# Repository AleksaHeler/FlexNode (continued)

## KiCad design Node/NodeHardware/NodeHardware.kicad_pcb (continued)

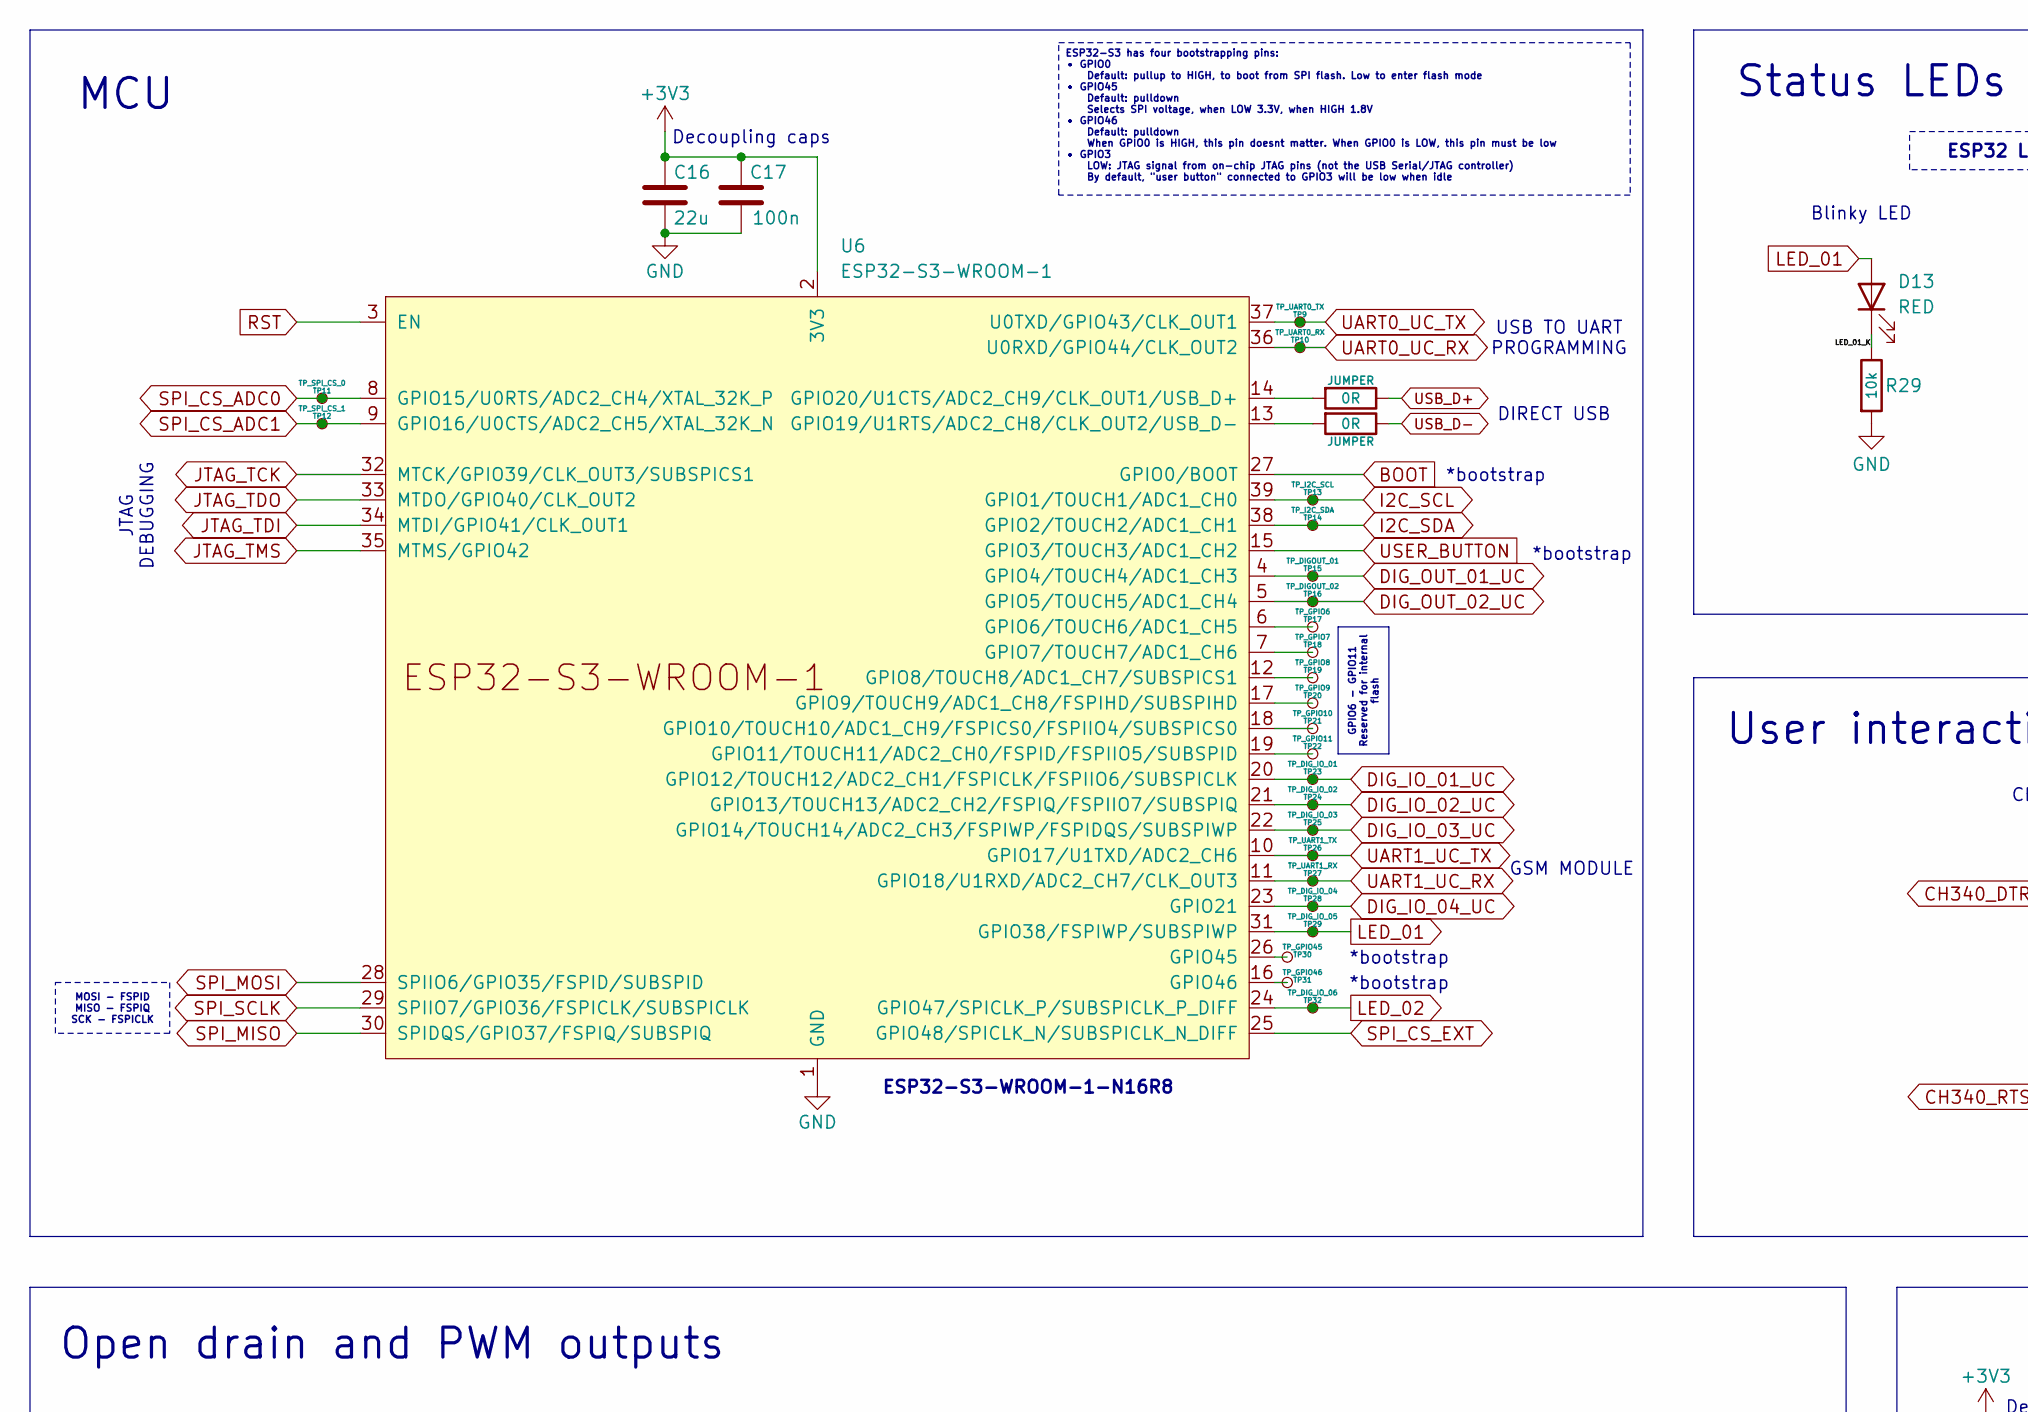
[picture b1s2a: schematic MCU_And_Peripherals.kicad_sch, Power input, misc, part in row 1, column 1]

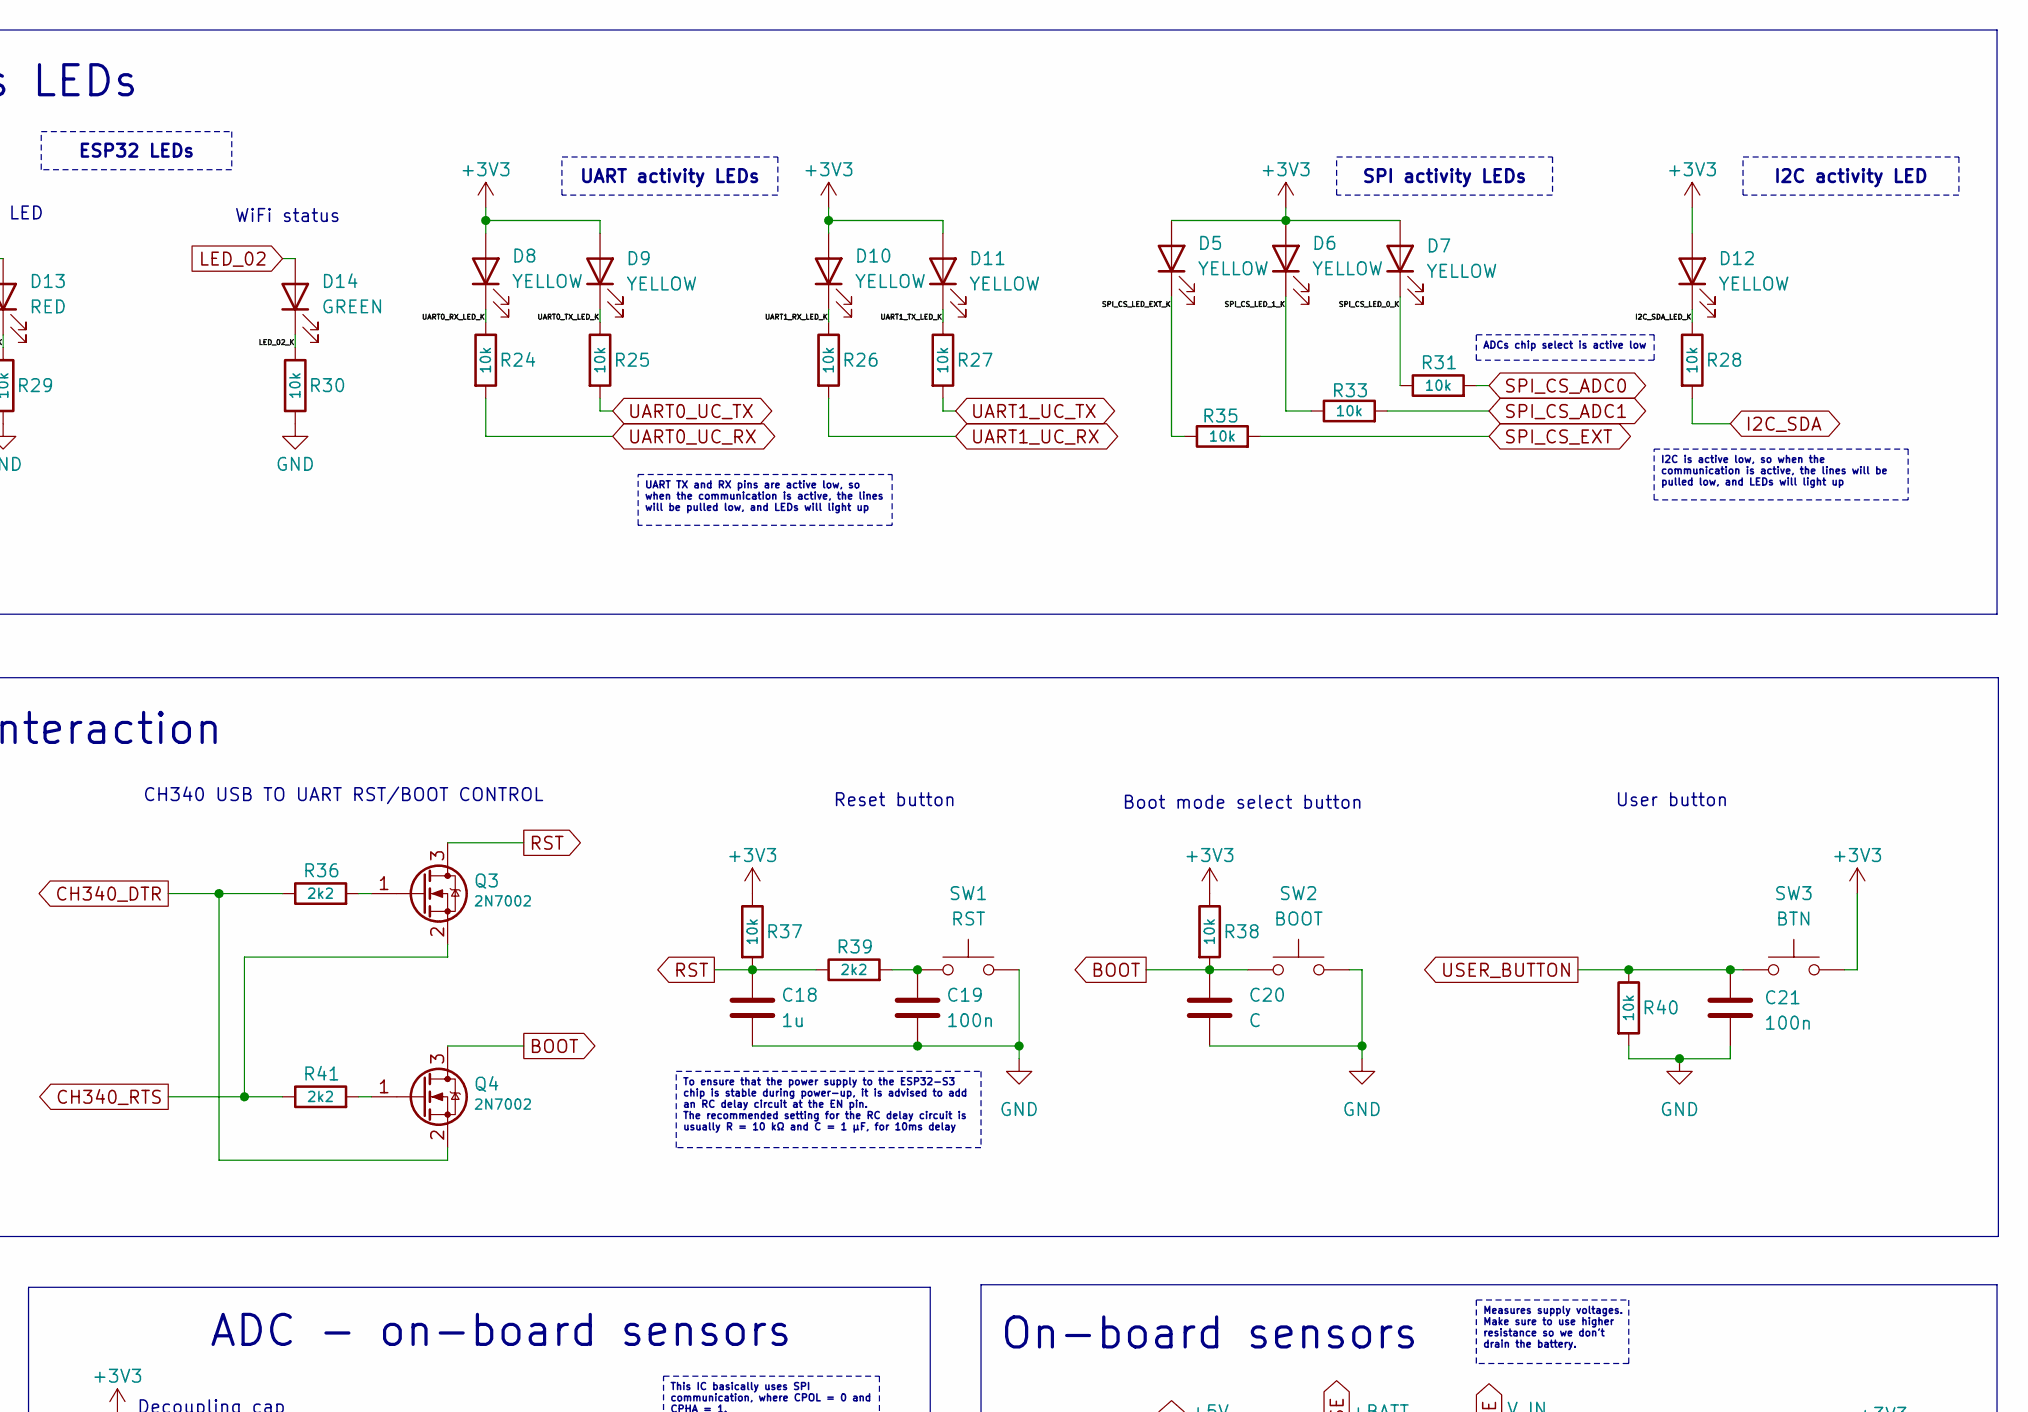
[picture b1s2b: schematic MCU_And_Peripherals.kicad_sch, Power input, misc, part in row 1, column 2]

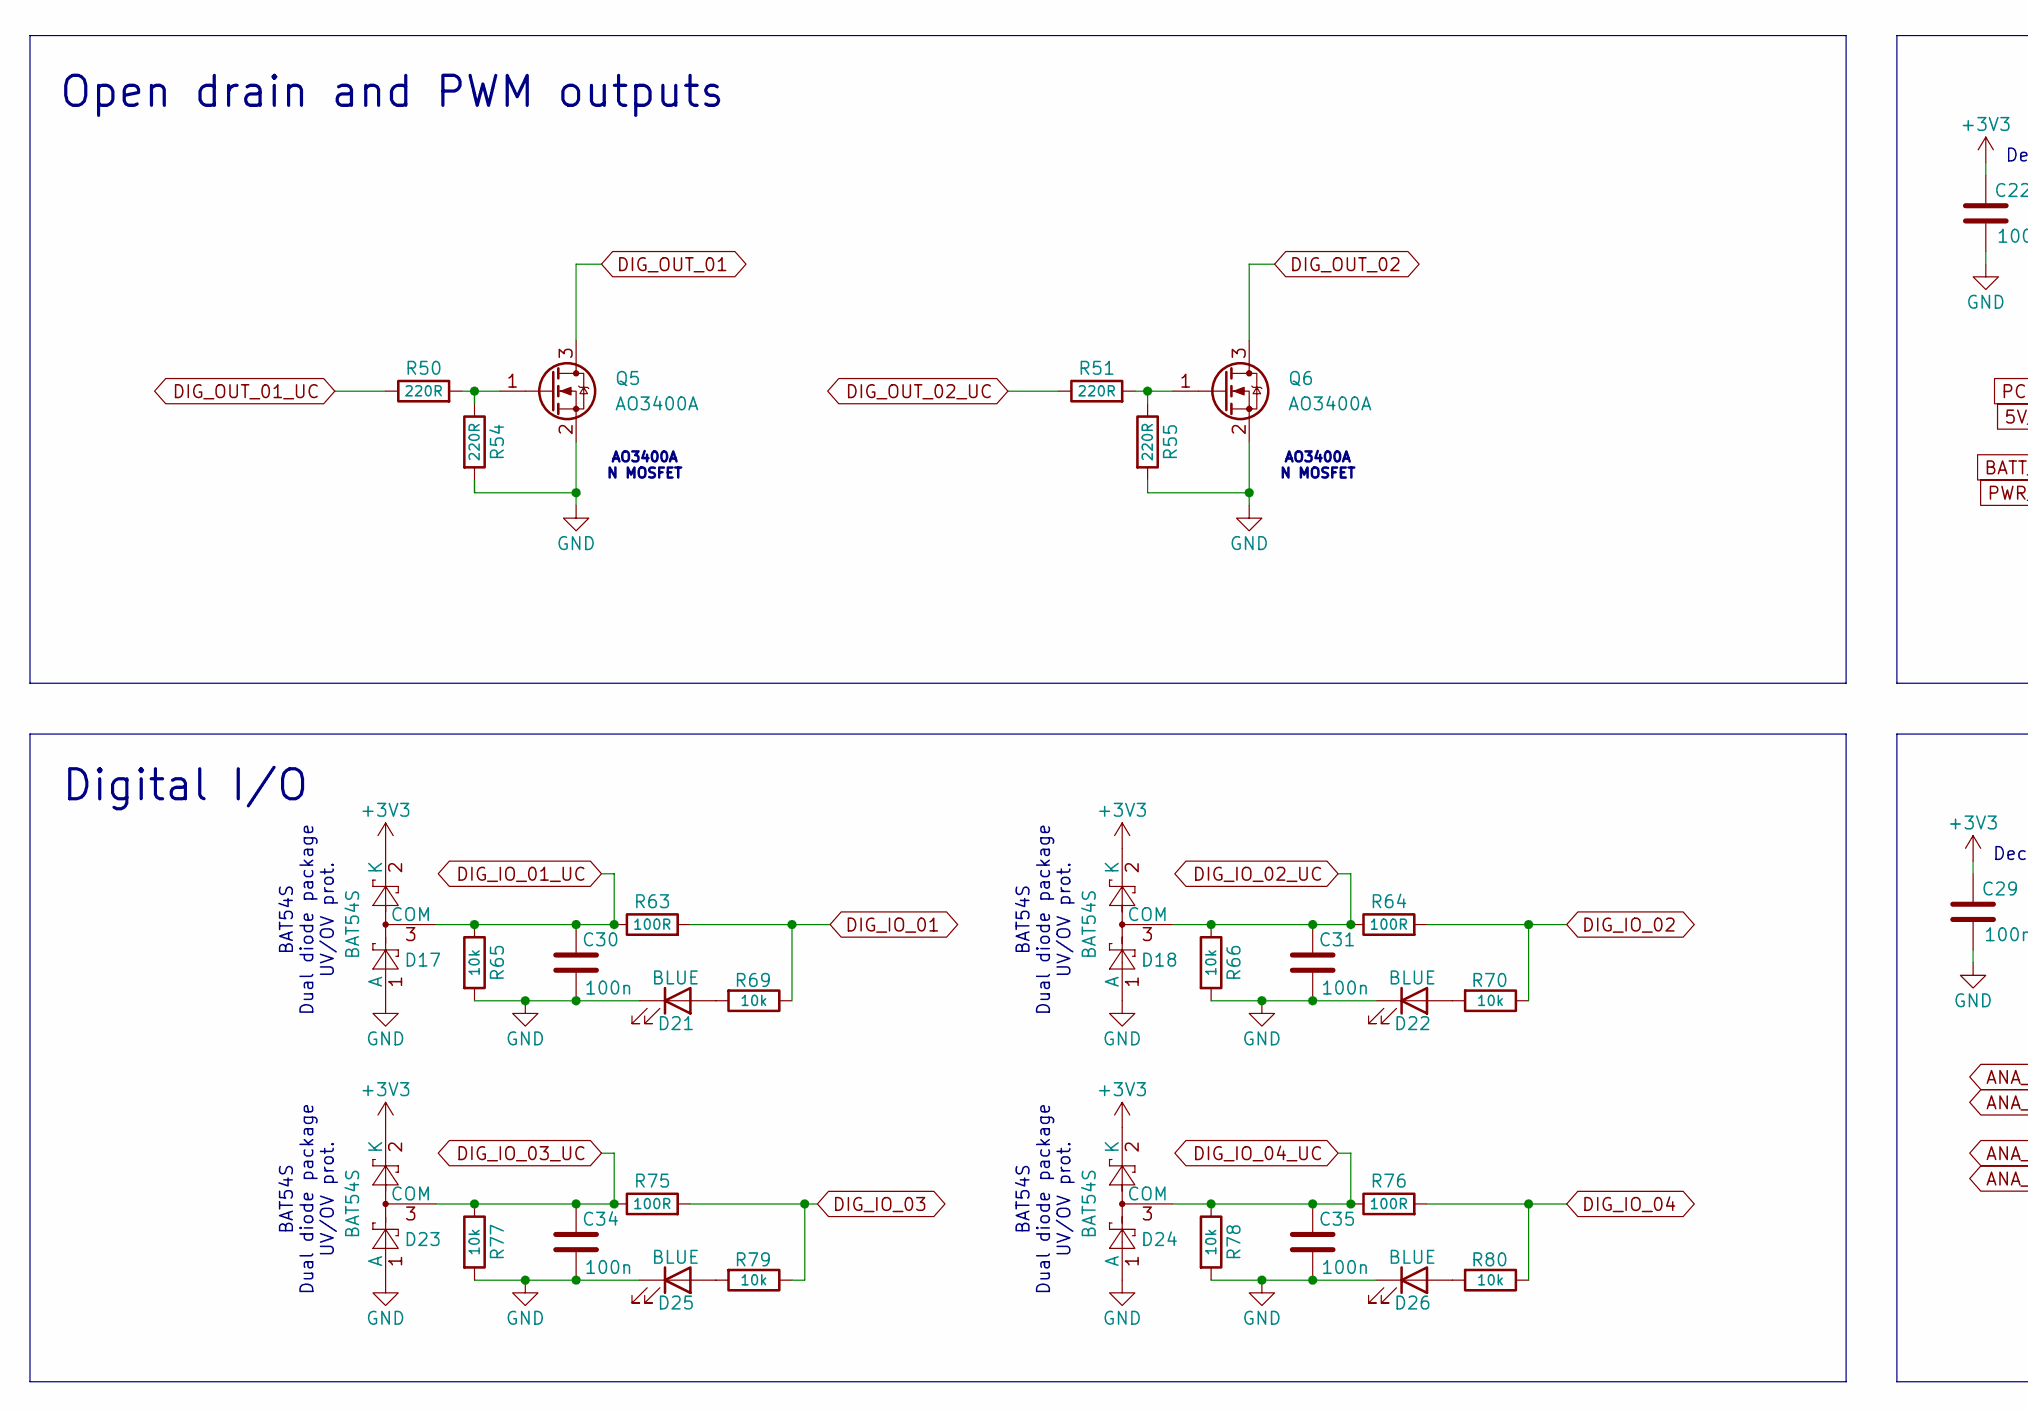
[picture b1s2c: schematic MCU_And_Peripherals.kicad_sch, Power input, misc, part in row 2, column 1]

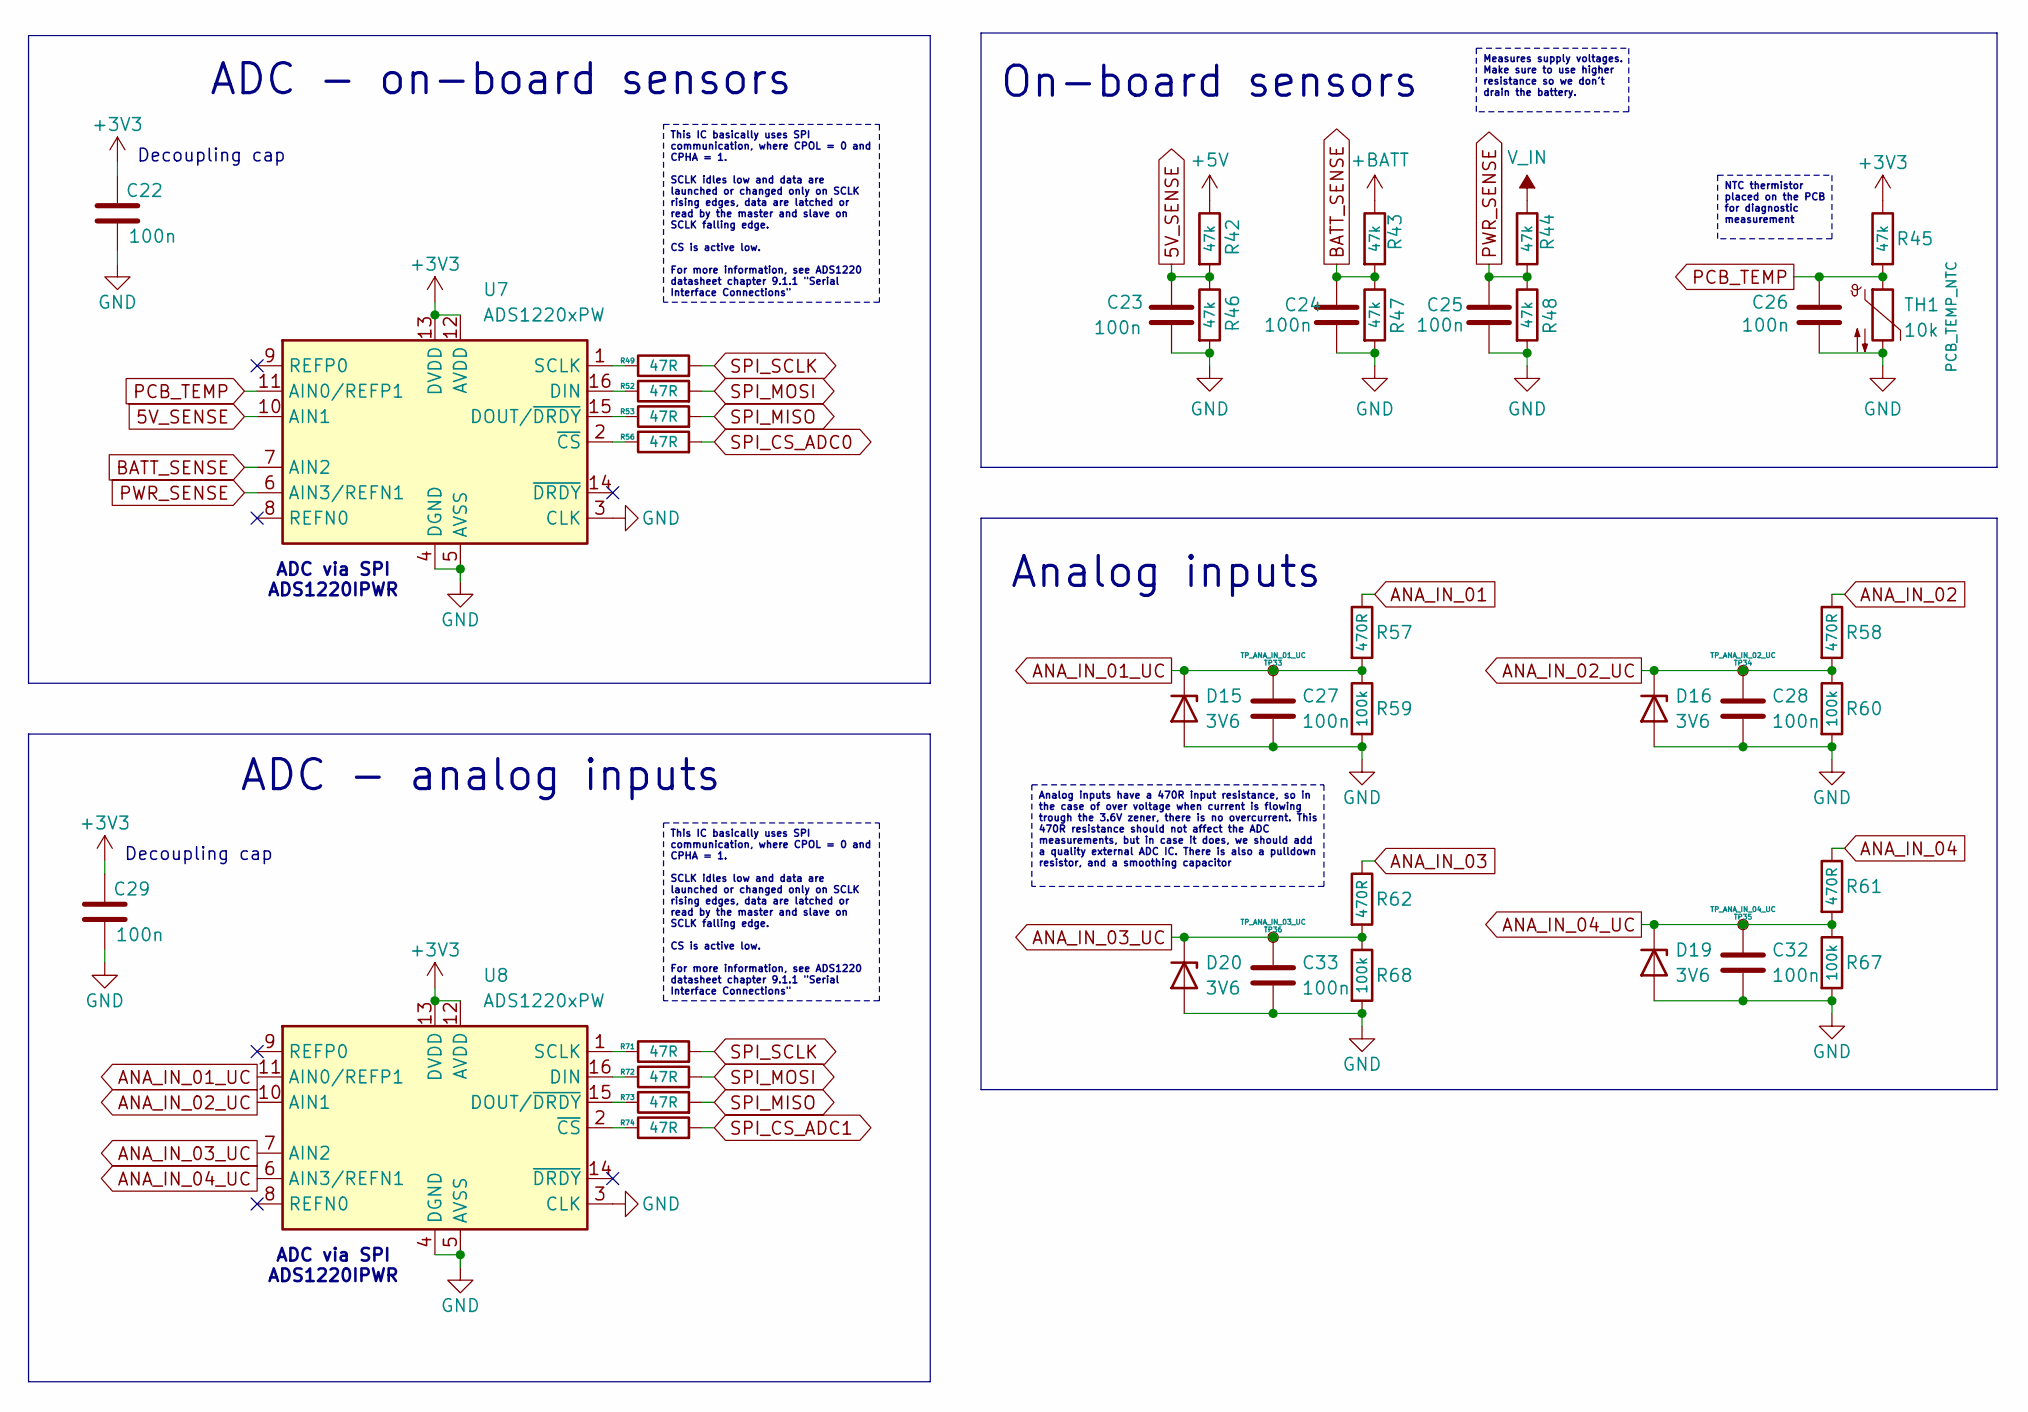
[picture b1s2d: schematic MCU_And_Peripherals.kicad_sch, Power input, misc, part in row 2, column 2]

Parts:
C16: 22u; C_0805_2012Metric
C17, C19, C21, C22, C23, C24, C25, C26, C27, C28, C29, C30, C31, C32, C33, C34, C35: 100n; C_0805_2012Metric
C18: 1u; C_0805_2012Metric
C20: C; C_0805_2012Metric
D5, D6, D7, D8, D9, D10, D11, D12: YELLOW; LED_1210_3225Metric
D13: RED; LED_1210_3225Metric
D14: GREEN; LED_1210_3225Metric
D15, D16, D19, D20: 3V6; D_SOD-123
D17, D18, D23, D24: BAT54S; SOT-23
D21, D22, D25, D26: BLUE; LED_1210_3225Metric
Q3, Q4: 2N7002; SOT-23
Q5, Q6: AO3400A; SOT-23
R24, R25, R26, R27, R28, R29, R30, R31, R33, R35, R37, R38, R40, R65, R66, R69, R70, R77, R78, R79, R80: 10k; R_0805_2012Metric
R32, R34: 0R; R_0805_2012Metric
R36, R39, R41: 2k2; R_0805_2012Metric
R42, R43, R44, R45, R46, R47, R48: 47k; R_0805_2012Metric
R49, R52, R53, R56, R71, R72, R73, R74: 47R; R_0805_2012Metric
R50, R51, R54, R55: 220R; R_0805_2012Metric
R57, R58, R61, R62: 470R; R_0805_2012Metric
R59, R60, R67, R68: 100k; R_0805_2012Metric
R63, R64, R75, R76: 100R; R_0805_2012Metric
SW1: RST; SW_Push_1P1T_NO_6x6mm_H9.5mm
SW2: BOOT; SW_Push_1P1T_NO_6x6mm_H9.5mm
SW3: BTN; SW_Push_1P1T_NO_6x6mm_H9.5mm
TH1: 10k; R_0805_2012Metric
TP9: TP_UART0_TX; TestPoint_Pad_D1.0mm
TP10: TP_UART0_RX; TestPoint_Pad_D1.0mm
TP11: TP_SPI_CS_0; TestPoint_Pad_D1.0mm
TP12: TP_SPI_CS_1; TestPoint_Pad_D1.0mm
TP13: TP_I2C_SCL; TestPoint_Pad_D1.0mm
TP14: TP_I2C_SDA; TestPoint_Pad_D1.0mm
TP15: TP_DIGOUT_01; TestPoint_Pad_D1.0mm
TP16: TP_DIGOUT_02; TestPoint_Pad_D1.0mm
TP17: TP_GPIO6; TestPoint_Pad_D1.0mm
TP18: TP_GPIO7; TestPoint_Pad_D1.0mm
TP19: TP_GPIO8; TestPoint_Pad_D1.0mm
TP20: TP_GPIO9; TestPoint_Pad_D1.0mm
TP21: TP_GPIO10; TestPoint_Pad_D1.0mm
TP22: TP_GPIO11; TestPoint_Pad_D1.0mm
TP23: TP_DIG_IO_01; TestPoint_Pad_D1.0mm
TP24: TP_DIG_IO_02; TestPoint_Pad_D1.0mm
TP25: TP_DIG_IO_03; TestPoint_Pad_D1.0mm
TP26: TP_UART1_TX; TestPoint_Pad_D1.0mm
TP27: TP_UART1_RX; TestPoint_Pad_D1.0mm
TP28: TP_DIG_IO_04; TestPoint_Pad_D1.0mm
TP29: TP_DIG_IO_05; TestPoint_Pad_D1.0mm
TP30: TP_GPIO45; TestPoint_Pad_D1.0mm
TP31: TP_GPIO46; TestPoint_Pad_D1.0mm
TP32: TP_DIG_IO_06; TestPoint_Pad_D1.0mm
TP33: TP_ANA_IN_01_UC; TestPoint_Pad_D1.0mm
TP34: TP_ANA_IN_02_UC; TestPoint_Pad_D1.0mm
TP35: TP_ANA_IN_04_UC; TestPoint_Pad_D1.0mm
TP36: TP_ANA_IN_03_UC; TestPoint_Pad_D1.0mm
U6: ESP32-S3-WROOM-1
U7, U8: ADS1220xPW; TSSOP-16_4.4x5mm_P0.65mm

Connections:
5V_SENSE: C23.1, R42.2, R46.1, U7.10 (AIN1)
+3V3: C16.2, C17.2, C22.2, C29.2, D5.2 (A), D6.2 (A), D7.2 (A), D8.2 (A), D9.2 (A), D10.2 (A), D11.2 (A), D12.2 (A), D17.2 (K), D18.2 (K), D23.2 (K), D24.2 (K), R37.1, R38.1, R45.1, SW3.2, U6.2 (3V3), U7.12 (AVDD), U7.13 (DVDD), U8.12 (AVDD), U8.13 (DVDD); also elsewhere on the board
+5V: R42.1; also elsewhere on the board
+BATT: R43.1; also elsewhere on the board
/MCU_And_Peripherals/I2C_SDA_LED_K: D12.1 (K), R28.1
/MCU_And_Peripherals/LED_01_K: D13.1 (K), R29.1
/MCU_And_Peripherals/LED_02_K: D14.1 (K), R30.1
/MCU_And_Peripherals/SPI_CS_LED_0_K: D7.1 (K), R31.1
/MCU_And_Peripherals/SPI_CS_LED_1_K: D6.1 (K), R33.1
/MCU_And_Peripherals/SPI_CS_LED_EXT_K: D5.1 (K), R35.1
/MCU_And_Peripherals/UART0_RX_LED_K: D8.1 (K), R24.1
/MCU_And_Peripherals/UART0_TX_LED_K: D9.1 (K), R25.1
/MCU_And_Peripherals/UART1_RX_LED_K: D10.1 (K), R26.1
/MCU_And_Peripherals/UART1_TX_LED_K: D11.1 (K), R27.1
ANA_IN_01: R57.1; also elsewhere on the board
ANA_IN_01_UC: C27.1, D15.1 (K), R57.2, R59.1, TP33.1, U8.11 (AIN0/REFP1)
ANA_IN_02: R58.1; also elsewhere on the board
ANA_IN_02_UC: C28.1, D16.1 (K), R58.2, R60.1, TP34.1, U8.10 (AIN1)
ANA_IN_03: R62.1; also elsewhere on the board
ANA_IN_03_UC: C33.1, D20.1 (K), R62.2, R68.1, TP36.1, U8.7 (AIN2)
ANA_IN_04: R61.1; also elsewhere on the board
ANA_IN_04_UC: C32.1, D19.1 (K), R61.2, R67.1, TP35.1, U8.6 (AIN3/REFN1)
BATT_SENSE: C24.1, R43.2, R47.1, U7.7 (AIN2)
BOOT: C20.1, Q4.3 (D), R38.2, SW2.1, U6.27 (GPIO0/BOOT)
CH340_DTR: Q4.2 (S), R36.1; also elsewhere on the board
CH340_RTS: Q3.2 (S), R41.1; also elsewhere on the board
DIG_IO_01: R63.2, R69.1; also elsewhere on the board
DIG_IO_01_UC: C30.1, D17.3 (COM), R63.1, R65.1, TP23.1, U6.20 (GPIO12/TOUCH12/ADC2_CH1/FSPICLK/FSPIIO6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)
DIG_IO_02: R64.2, R70.1; also elsewhere on the board
DIG_IO_02_UC: C31.1, D18.3 (COM), R64.1, R66.1, TP24.1, U6.21 (GPIO13/TOUCH13/ADC2_CH2/FSPIQ/FSPIIO7/S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)
DIG_IO_03: R75.2, R79.1; also elsewhere on the board
DIG_IO_03_UC: C34.1, D23.3 (COM), R75.1, R77.1, TP25.1, U6.22 (GPIO14/TOUCH14/ADC2_CH3/FSPIWP/FSPIDQS/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)
DIG_IO_04: R76.2, R80.1; also elsewhere on the board
DIG_IO_04_UC: C35.1, D24.3 (COM), R76.1, R78.1, TP28.1, U6.23 (GPIO21)
DIG_OUT_01: Q5.3 (D); also elsewhere on the board
DIG_OUT_01_UC: R50.1, TP15.1, U6.4 (GPIO4/TOUCH4/ADC1_CH3)
DIG_OUT_02: Q6.3 (D); also elsewhere on the board
DIG_OUT_02_UC: R51.1, TP16.1, U6.5 (GPIO5/TOUCH5/ADC1_CH4)
GND: C16.1, C17.1, C18.2, C19.2, C20.2, C21.2, C22.1, C23.2, C24.2, C25.2, C26.2, C27.2, C28.2, C29.1, C30.2, C31.2, C32.2, C33.2, C34.2, C35.2, D15.2 (A), D16.2 (A), D17.1 (A), D18.1 (A), D19.2 (A), D20.2 (A), D21.1 (K), D22.1 (K), D23.1 (A), D24.1 (A), D25.1 (K), D26.1 (K), Q5.2 (S), Q6.2 (S), R29.2, R30.2, R40.2, R46.2, R47.2, R48.2, R54.2, R55.2, R59.2, R60.2, R65.2, R66.2, R67.2, R68.2, R77.2, R78.2, SW1.2, SW2.2, TH1.2, U6.1 (GND), U6.40 (GND), U6.41 (GND), U7.3 (CLK), U7.4 (DGND), U7.5 (AVSS), U8.3 (CLK), U8.4 (DGND), U8.5 (AVSS); also elsewhere on the board
I2C_SCL: TP13.1, U6.39 (GPIO1/TOUCH1/ADC1_CH0); also elsewhere on the board
I2C_SDA: R28.2, TP14.1, U6.38 (GPIO2/TOUCH2/ADC1_CH1); also elsewhere on the board
JTAG_TCK: U6.32 (MTCK/GPIO39/CLK_OUT3/SUBSPICS1); also elsewhere on the board
JTAG_TDI: U6.34 (MTDI/GPIO41/CLK_OUT1); also elsewhere on the board
JTAG_TDO: U6.33 (MTDO/GPIO40/CLK_OUT2); also elsewhere on the board
JTAG_TMS: U6.35 (MTMS/GPIO42); also elsewhere on the board
LED_01: D13.2 (A), TP29.1, U6.31 (GPIO38/FSPIWP/SUBSPIWP)
LED_02: D14.2 (A), TP32.1, U6.24 (GPIO47/SPICLK_P/SUBSPICLK_P_DIFF)
unnamed: C19.1, R39.2, SW1.1
unnamed: D21.2 (A), R69.2
unnamed: D22.2 (A), R70.2
unnamed: D25.2 (A), R79.2
unnamed: D26.2 (A), R80.2
unnamed: Q3.1 (G), R36.2
unnamed: Q4.1 (G), R41.2
unnamed: Q5.1 (G), R50.2, R54.1
unnamed: Q6.1 (G), R51.2, R55.1
unnamed: TP17.1, U6.6 (GPIO6/TOUCH6/ADC1_CH5)
unnamed: TP18.1, U6.7 (GPIO7/TOUCH7/ADC1_CH6)
unnamed: TP19.1, U6.12 (GPIO8/TOUCH8/ADC1_CH7/SUBSPICS1)
unnamed: TP20.1, U6.17 (GPIO9/TOUCH9/ADC1_CH8/FSPIHD/SUBSPIHD)
unnamed: TP21.1, U6.18 (GPIO10/TOUCH10/ADC1_CH9/FSPICS0/FSPIIO4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)
unnamed: TP22.1, U6.19 (GPIO11/TOUCH11/ADC2_CH0/FSPID/FSPIIO5/S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)
unnamed: R34.2, U6.13 (GPIO19/U1RTS/ADC2_CH8/CLK_OUT2/USB_D-)
unnamed: R32.2, U6.14 (GPIO20/U1CTS/ADC2_CH9/CLK_OUT1/USB_D+)
unnamed: TP30.1, U6.26 (GPIO45)
unnamed: TP31.1, U6.16 (GPIO46)
unnamed: R52.1, U7.16 (DIN)
unnamed: R53.1, U7.15 (DOUT/~DRDY)
unnamed: R49.1, U7.1 (SCLK)
unnamed: R56.1, U7.2 (~CS)
unnamed: R72.1, U8.16 (DIN)
unnamed: R73.1, U8.15 (DOUT/~DRDY)
unnamed: R71.1, U8.1 (SCLK)
unnamed: R74.1, U8.2 (~CS)
PCB_TEMP: C26.1, R45.2, TH1.1, U7.11 (AIN0/REFP1)
PWR_SENSE: C25.1, R44.2, R48.1, U7.6 (AIN3/REFN1)
RST: C18.1, Q3.3 (D), R37.2, R39.1, U6.3 (EN); also elsewhere on the board
SPI_CS_ADC0: R31.2, R56.2, TP11.1, U6.8 (GPIO15/U0RTS/ADC2_CH4/XTAL_32K_P)
SPI_CS_ADC1: R33.2, R74.2, TP12.1, U6.9 (GPIO16/U0CTS/ADC2_CH5/XTAL_32K_N)
SPI_CS_EXT: R35.2, U6.25 (GPIO48/SPICLK_N/SUBSPICLK_N_DIFF); also elsewhere on the board
SPI_MISO: R53.2, R73.2, U6.30 (SPIDQS/GPIO37/FSPIQ/SUBSPIQ); also elsewhere on the board
SPI_MOSI: R52.2, R72.2, U6.28 (SPIIO6/GPIO35/FSPID/SUBSPID); also elsewhere on the board
SPI_SCLK: R49.2, R71.2, U6.29 (SPIIO7/GPIO36/FSPICLK/SUBSPICLK); also elsewhere on the board
UART0_UC_RX: R24.2, TP10.1, U6.36 (U0RXD/GPIO44/CLK_OUT2); also elsewhere on the board
UART0_UC_TX: R25.2, TP9.1, U6.37 (U0TXD/GPIO43/CLK_OUT1); also elsewhere on the board
UART1_UC_RX: R26.2, TP27.1, U6.11 (GPIO18/U1RXD/ADC2_CH7/CLK_OUT3); also elsewhere on the board
UART1_UC_TX: R27.2, TP26.1, U6.10 (GPIO17/U1TXD/ADC2_CH6); also elsewhere on the board
USB_D+: R32.1; also elsewhere on the board
USB_D-: R34.1; also elsewhere on the board
USER_BUTTON: C21.1, R40.1, SW3.1, U6.15 (GPIO3/TOUCH3/ADC1_CH2)
V_IN: R44.1; also elsewhere on the board

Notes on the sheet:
ESP32 LEDs
This IC basically uses SPI communication, where CPOL = 0 and CPHA = 1. SCLK idles low and data are launched or changed only on SCLK rising edges, data are latched or read by the master and slave on SCLK falling edge. CS is active low. For more information, see ADS1220 datasheet chapter 9.1.1 "Seria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
NTC thermistor placed on the PCB for diagnostic measurement
UART activity LEDs
SPI activity LEDs
Measures supply voltages. Make sure to use higher resistance so we don't drain the battery.
Analog inputs have a 470R input resistance, so in the case of over voltage when current is flowing trough the 3.6V zener, there is no overcurrent. This 470R resistance should not affect the ADC measurements, but in case it does, we should add a quality external ADC IC. There is also a pulldown resi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
To ensure that the power supply to the ESP32-S3 chip is stable during power-up, it is advised to add an RC delay circuit at the EN pin. The recommended setting for the RC delay circuit is usually R = 10 kΩ and C = 1 μF, for 10ms delay
I2C activity LED
UART TX and RX pins are active low, so when the communication is active, the lines will be pulled low, and LEDs will light up
I2C is active low, so when the communication is active, the lines will be pulled low, and LEDs will light up
GPIO6 - GPIO11 Reserved for internal flash
ADCs chip select is active low
ESP32-S3 has four bootstrapping pins: • GPIO0 Default: pullup to HIGH, to boot from SPI flash. Low to enter flash mode • GPIO45 Default: pulldown Selects SPI voltage, when LOW 3.3V, when HIGH 1.8V • GPIO46 Default: pulldown When GPIO0 is HIGH, this pin doesnt matter. When GPIO0 is LOW, this pin mus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
MOSI - FSPID MISO - FSPIQ SCK - FSPICLK
USB TO UART PROGRAMMING
ADC via SPI ADS1220IPWR
DIRECT USB
User interaction
*bootstrap
JTAG DEBUGGING
MCU
AO3400A N MOSFET
BAT54S Dual diode package UV/OV prot.
User button
CH340 USB TO UART RST/BOOT CONTROL
ESP32-S3-WROOM-1-N16R8
Decoupling cap
WiFi status
Reset button
ADC - on-board sensors
Blinky LED
On-board sensors
Decoupling caps
Status LEDs
Digital I/O
Open drain and PWM outputs
GSM MODULE
ADC - analog inputs
Analog inputs

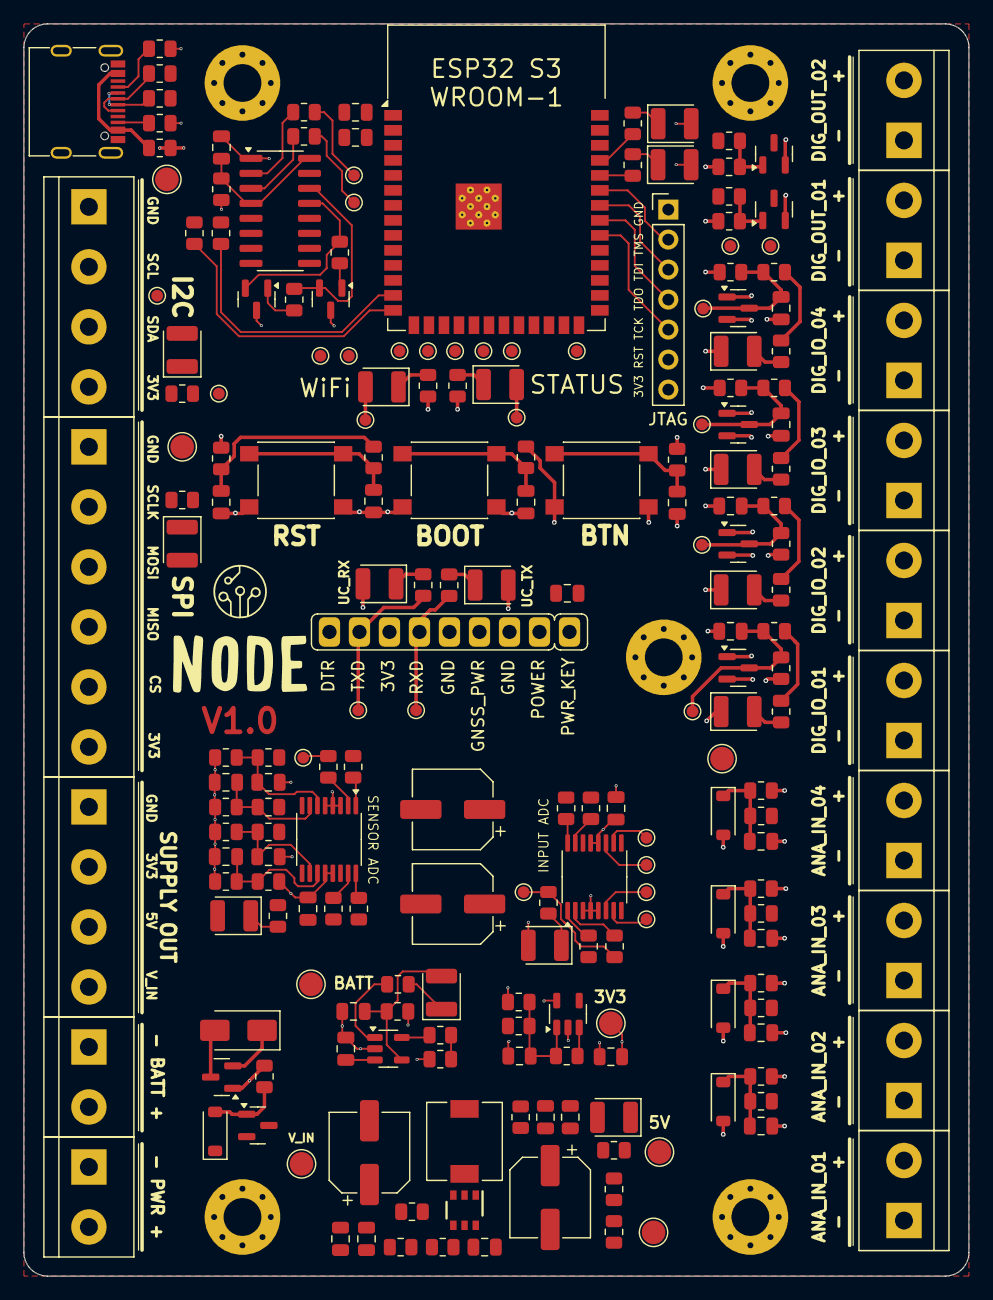
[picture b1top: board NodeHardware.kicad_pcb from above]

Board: 4 copper layers, 80.0 x 106.0 mm, 219 parts (0 on the bottom side), 116 nets.

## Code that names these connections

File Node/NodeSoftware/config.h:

#ifndef FLEX_CONFIG_H
#define FLEX_CONFIG_H

/*******************************************************/
/*** TIMING DEFINES ************************************/
/*******************************************************/

/* Baudrate used for serial communication */
#define SERIAL_BAUDRATE (115200)

/* Cycle time of the main program loop (ms). Set to 1s, as we don't need faster handling */
/* Other sensors might rely on thei 'Handle' functions being called exactly every 1s (led blinking, active wait, etc.) */
/* Usually more than 100ms is needed to do everything in a loop, but that has to be measured for specifc scenarios */
#define MAIN_CYCLE_TIME (1000)

/* How much to wait between two MQTT frames (ms) */
#define SEND_DELAY (300 * 1000)        /* Every 5min == 300s */

/* Cycle time of the debug loop (printing log to serial) in ms */
#define DEBUG_CYCLE_TIME (5 * 1000)    /* Print to Serial every 5s */


/*******************************************************/
/*** PIN DEFINES ***************************************/
/*******************************************************/

/* Pin to which the system status LED is connected */
#define SYSTEM_STATUS_LED_PIN 35

/* Pin to which the system status LED is connected */
#define WIFI_STATUS_LED_PIN 4

/* DHT22 connected to pin GPIO20 */
#define DHT22_PIN  20

/* NTC thermistor to measure PCB temp is connected to... */
#define PCB_TEMP_PIN 18

/* Presence sensor is connected to... */
#define PRESENCE_SENSOR_PIN 2

/* Light dependent resistor is connected to... */
#define LIGHT_SENSOR_PIN 1

/* Pin to which the MQ-2 gas sensor is connected */
#define AIR_QUALITY_SENSOR_PIN 5

/* BMP-280 is connected via I2C: */
/* SDA - GPIO8 */
/* SCL - GPIO9 */


#endif /* #ifndef FLEX_CONFIG_H */

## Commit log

2024-07-26 Initial system requirement start
2024-07-28 Continue working on requirements
2024-07-28 Update system requirement (finish version 1)
2024-07-30 Added basic KiCAD project and started adding items
2024-07-31 Finish all the basic SCHM needed for the ESP32
2024-07-31 Finish first version of inputs
2024-07-31 added some useful reference materials for ESP32 S3 deep sleep RTC, extPin, timer, wake up implementation, added application notes for SIM7000 GSM modem
2024-07-31 added my custom kicad components, and esp_board project to be a reference as it has a very similar concept to this project.
2024-07-31 added some comments and sim module to schematic
2024-08-04 Add a comment
2024-08-04 Cleanup and update gitignore
2024-08-04 Additional cleanup
2024-08-04 continued cleanup
2024-08-04 Schm cleanup and commenting
2024-08-28 Update SCHM (psu, cleanup), add datasheets
2024-08-31 Continue updating schm for initial version
2024-08-31 Continue schm update, slow progress
2024-09-01 Never ending SCHM design
2024-09-17 Halfway working on PCB for Node
2024-09-21 Add sample code for ESP32 Node
2024-09-21 Create basic admin.h as example
2024-09-21 Rename admin.h to admin_example.h
2024-09-21 Continue updating PCB (main form)
2024-09-24 Finish v1 of PCB layout
2024-10-07 Update SW side of the Node
    Still a lot of cleanup and work remains
2024-10-12 Update SW side
    Still bugs present
2024-10-15 Update SW to actually work!
2024-10-19 Add POC images
2024-10-21 Update SW a lot
    Using classes now, and dynamically creating all driver/sensors
2024-10-31 Update dht sens name, and presence calculation
